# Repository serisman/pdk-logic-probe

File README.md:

# pdk-logic-probe
A simple logic probe, based on the ultra-inexpensive (~$0.03) Padauk microcontrollers.
- LED is Green when Probe pin is LOW.
- LED is Red when Probe pin is HIGH.
- LED is Blue when Probe pin is Floating.

### Links
- [Firmware](firmware/)
- [PCB](pcb/)

### Schematic
(for 8-pin PFS154, PFS173, PMS150C/PMS15A, PMS152, PMS154C, PMS171B)

### Usage
Connect (-) to GND and (+) to VCC
- LED is Green when Probe pin is LOW.
- LED is Red when Probe pin is HIGH.
- LED is Blue when Probe pin is Floating.

### Compatibility
This project is currently intended to be run (without modifications) on the PFS154, PFS173, PMS150C/PMS15A, PMS152, PMS154C, and PMS171B Padauk microcontrollers,
but it should be able to be modified to run on just about every currently known Padauk microcontroller that is supported by SDCC and the Easy PDK Programmer.

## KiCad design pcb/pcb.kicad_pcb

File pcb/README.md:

# pcb ([pdk-logic-probe](https://github.com/serisman/pdk-logic-probe/))

### Schematic
(for 8-pin PFS154, PFS173, PMS150C, PMS15A, PMS152, PMS154C, PMS171B)

### PCB

This PCB design was created with KiCad, and has been [shared on OSHPARK](https://oshpark.com/shared_projects/ogOTS65P).
There are also gerber files available in the [output/gerber/](output/gerber/) directory, or [gerber.zip](output/gerber.zip).

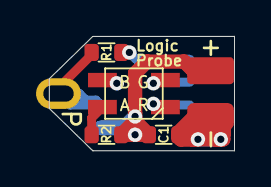
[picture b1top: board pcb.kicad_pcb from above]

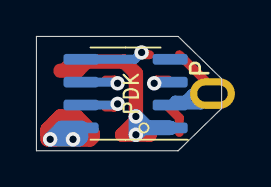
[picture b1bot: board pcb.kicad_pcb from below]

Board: 2 copper layers, 10.3 x 6.4 mm, 7 parts (2 on the bottom side), 8 nets.

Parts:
C1: 100n; C_0603
D1: LED_BAGR; LED_BAGR_3528
J1: PWR; PinHeader_1x02_P2.54mm_Horizontal
R1: 22k; R_0603
R2: 680; R_0603
TP1: Probe; PinHeader_1x01_P2.54mm_Vertical
U1: PDK; SOIC-8_3.9x4.9mm_P1.27mm

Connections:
GND: C1.2, J1.1, U1.8
LED_B: D1.1, U1.3
LED_G: D1.3, U1.6
LED_R: D1.4, U1.7
unnamed: D1.2, R2.2
unnamed: R1.1, U1.5
PROBE: R1.2, TP1.1, U1.2
VCC: C1.1, J1.2, R2.1, U1.1

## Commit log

2022-12-21 Initial Version
2022-12-21 Tweak README.md
